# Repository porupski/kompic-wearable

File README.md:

# Kompic̄ &nbsp;·&nbsp; Mk1b

**Compact Open Multisensor Platform & Apparatus**

*/ˈkompitɕ/* — Croatian for "little computer" (and the word you'd only use for an actual friend, not a stranger).

A fully open-source, offline-first, ML-capable wrist-mounted sensor platform. The hardware collects. The firmware infers. You own everything.

> **Internal hardware version:** `iv8.0` — tracked in the docs to keep the PCBs matched across revisions.

Page: [https://porupski.github.io/kompic-wearable/](https://porupski.github.io/kompic-wearable/)

---

## What it is

Kompic̄ is a wrist-mounted sensor platform built around an **ESP32-S3** (dual-core, 8 MB PSRAM, 16 MB flash) with a sensor suite denser than any open-source watch, and enough on-device compute to run real neural networks on that data — sleep staging, sound classification, sensor fusion — all locally, all offline, all inspectable.

Currently on its second hardware revision, **Mk1b (`iv8.0`)**: all ten I²C sensors bring up clean, the AMOLED display and touch panel run a working LVGL interface, and GPS streams live fixes.

It is **not** a companion in the AI sense and **not** a phone accessory. It runs standalone. BLE is a capability, not a requirement. There is no cloud, no subscription, no account.

### Philosophy

- **Open source** — hardware (KiCad), firmware, ML models, and case design. Everything inspectable, modifiable, forkable.
- **Offline first** — works fully standalone. No phone, no cloud, no subscription.
- **Raw data access** — PPG waveforms, IMU streams, mic audio, environmental readings. Not just processed metrics.
- **ML-native** — the compute surplus exists specifically to run on-device inference.

---

## Hardware at a glance

| Domain | Detail |
|--------|--------|
| MCU | ESP32-S3 dual-core Xtensa LX7 @ 240 MHz, 8 MB PSRAM, 16 MB flash |
| Storage | MicroSD (128 GB+) |
| Connectivity | BLE 5.x |
| Display | 2.06" rectangular AMOLED, 45.6 × 37.3 mm glass, QSPI |
| PCBs | Two 1.0 mm 4-layer boards: main board + skin-facing daughter board |
| Case | Two-piece SLM titanium (Ti-6Al-4V), ~48 × 40 × 12 mm |
| Weight | 33 g watch body, 56 g with straps |
| Power | ~300 mAh LiPo, USB-C charging, fuel gauge |

### Sensor suite

| Sensor | Part | Measures |
|--------|------|----------|
| ❤️ Optical HR / SpO2 | MAX30101 | Heart rate, HRV, blood oxygen, PPG waveforms |
| 🏃 IMU | LSM6DSV16X | Accel, gyro, on-chip decision trees |
| 🔋 Fuel gauge | MAX17048G | Battery state-of-charge, cell voltage |
| 🌡️ Skin temperature | TMP117 | High-precision skin temp trending |
| 🧭 Magnetometer | LIS3MDLTR | Compass heading, magnetic anomaly |
| 🛰️ GPS | u-blox M10S | Position, velocity, atomic time sync |
| 🌍 Environmental | BME688 | Temp, pressure, humidity, VOC / air quality |
| 💡 Ambient light | VEML6030 | Lux level, display brightness |
| 🎤 MEMS microphone | MSM261DGT003 | Audio capture, noise level, sound classification |
| 📳 Haptics | ELV1411A + DRV2605L | Vibration patterns, alerts, smart wake |
| 🔦 Flashlight | White LED + BC847C driver | Utility light |
| 🚦 Status LED | RGB LED | Notification / mode indicator |

---

## Repository layout

```

kompic-wearable/
├── hardware/    KiCad schematics, PCB layout, production files   [CERN-OHL-S v2]
├── firmware/    ESP32-S3 dual-core firmware, ML models           [GPLv3]
├── case/        Onshape / 3D-printable case models               [CC BY-SA 4.0]
└── docs/        Documentation site (GitHub Pages) + images       [CC BY-SA 4.0]

```

---

## Project status

In active development. Hardware bring-up and verification underway for **Mk1b (`iv8.0`)**.

| Area | Status |
|------|--------|
| Circuit + PCB | Mk1 done (schematics, power tree, KiCad source) - needs update to Mk1b |
| Fabrication + assembly | Mk1 done (JLCPCB process, BOM, production files) - needs update to Mk1b |
| Manual assembly | Planned |
| 3D models + case | Planned ([View on Onshape](https://cad.onshape.com/documents/2e7ed980a6b60d585006763f/w/61a5aff226ec4b8dea793e41/e/49d622626b42dd5951f83a04?renderMode=0&uiState=6ab1d153fa1f2d90dd14641c)) |
| Firmware | In progress (I²C drivers, LVGL 9 display + touch UI, GPS UBX/NMEA parsing) |

Check the Development page for info on current stage of the project.

Documentation: **[https://porupski.github.io/kompic-wearable/](https://porupski.github.io/kompic-wearable/)**

---

## Author & License

Hardware, firmware, case, and webpage design by **Ivan Porupski**, 2026.

## License

Kompic̄ is released under three copyleft licenses, one per kind of material. All three keep the project open and require attribution — anyone may use, modify, build on, and even sell derivatives, **provided they keep their version equally open and credit the original author.**

| Part of the project | License | What it means in one line |
|---------------------|---------|---------------------------|
| **Hardware** (`/hardware`) | [CERN-OHL-S v2](https://ohwr.org/cern_ohl_s_v2.txt) | Make/modify/sell boards freely; distributed modifications must publish their full design files under the same license. |
| **Firmware** (`/firmware`) | [GPLv3](https://www.gnu.org/licenses/gpl-3.0.html) | Run/modify/redistribute freely; distributed modifications must publish full source under GPLv3. |
| **Docs & 3D / case** (`/docs`, `/case`) | [CC BY-SA 4.0](https://creativecommons.org/licenses/by-sa/4.0/) | Reuse/remix freely with credit; shared derivatives stay under CC BY-SA. |

GitHub displays **GPL-3.0** as the repository's headline license; the per-folder breakdown above is authoritative. See [`LICENSING.md`](LICENSING.md) for details.

**Copyright © 2026 Ivan Porupski.** Each contributor retains copyright on their own contributions; the whole project remains under the copyleft licenses above.

There is no separate commercial license and no contributor license agreement (CLA). Contributions are accepted under the same licenses as the files they touch (inbound = outbound).

---

## Contributing

Contributions are welcome. By submitting a contribution you agree it is licensed under the same license that already covers the file(s) you are changing (see table above). Keep copyright and license notices intact.

---

## Disclaimer

Kompic̄ is **not a medical device** and is not intended to diagnose, treat, or prevent any condition. All work with these electronics and lithium batteries is done at your own risk. The author and contributors are not liable for any direct, indirect, incidental, or consequential damages.

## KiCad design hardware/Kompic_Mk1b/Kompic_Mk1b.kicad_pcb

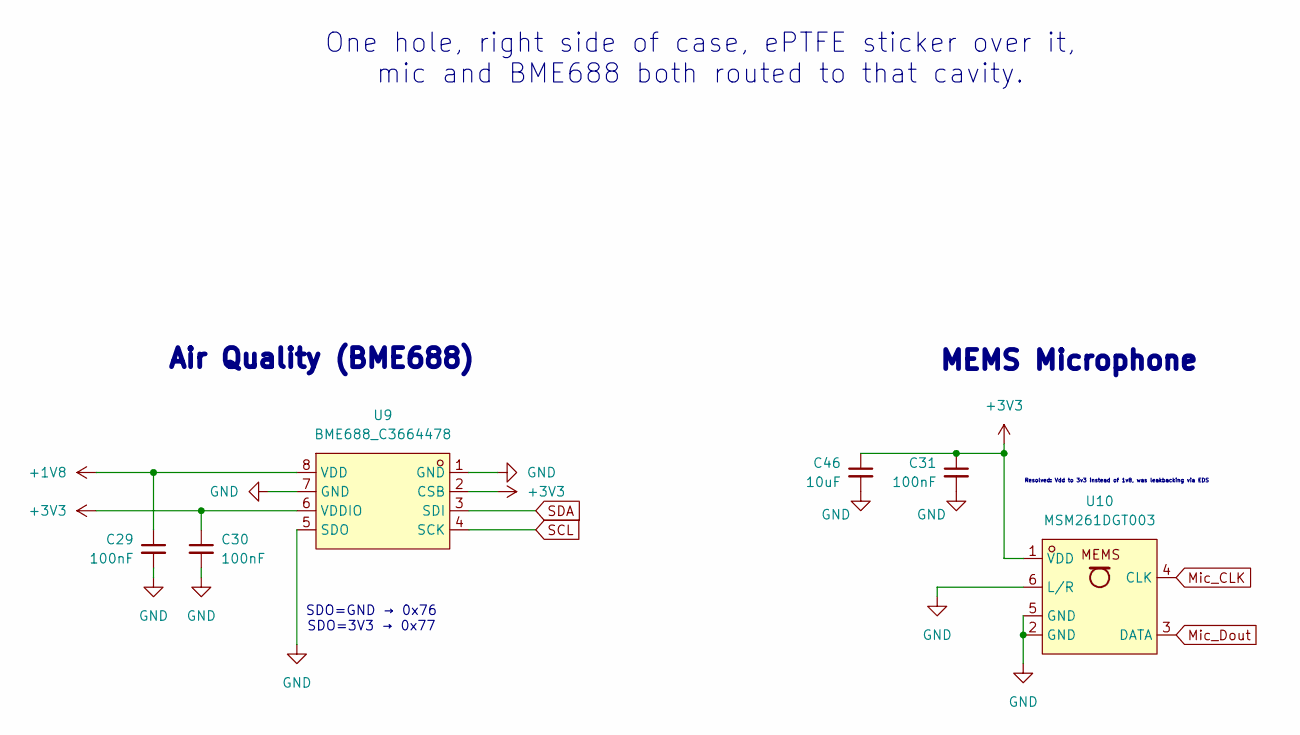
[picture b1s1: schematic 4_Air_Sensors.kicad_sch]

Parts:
C29, C30, C31: 100nF; C_0402_1005Metric_Pad0.74x0.62mm_HandSolder
C46: 10uF; C_0402_1005Metric_Pad0.74x0.62mm_HandSolder
U9: BME688_C3664478; LGA-8_L3.0-W3.0-P0.80_BME688; LCSC Part C3664478
U10: MSM261DGT003; MIC-SMD_6P-L4.0-W2.0_LMD4020T261-OC3; LCSC Part C48227730

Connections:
+1V8: C29.1, U9.8 (VDD); also elsewhere on the board
+3V3: C30.1, C31.1, C46.1, U9.2 (CSB), U9.6 (VDDIO), U10.1 (VDD); also elsewhere on the board
GND: C29.2, C30.2, C31.2, C46.2, U9.1 (GND), U9.5 (SDO), U9.7 (GND), U10.2 (GND), U10.5 (GND), U10.6 (L/R); also elsewhere on the board
Mic_CLK: U10.4 (CLK); also elsewhere on the board
Mic_Dout: U10.3 (DATA); also elsewhere on the board
SCL: U9.4 (SCK); also elsewhere on the board
SDA: U9.3 (SDI); also elsewhere on the board

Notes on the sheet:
Air Quality (BME688)
SDO=GND → 0x76 SDO=3V3 → 0x77
One hole, right side of case, ePTFE sticker over it, mic and BME688 both routed to that cavity.
MEMS Microphone
Resolved: Vdd to 3v3 instead of 1v8, was leakbacking via EDS

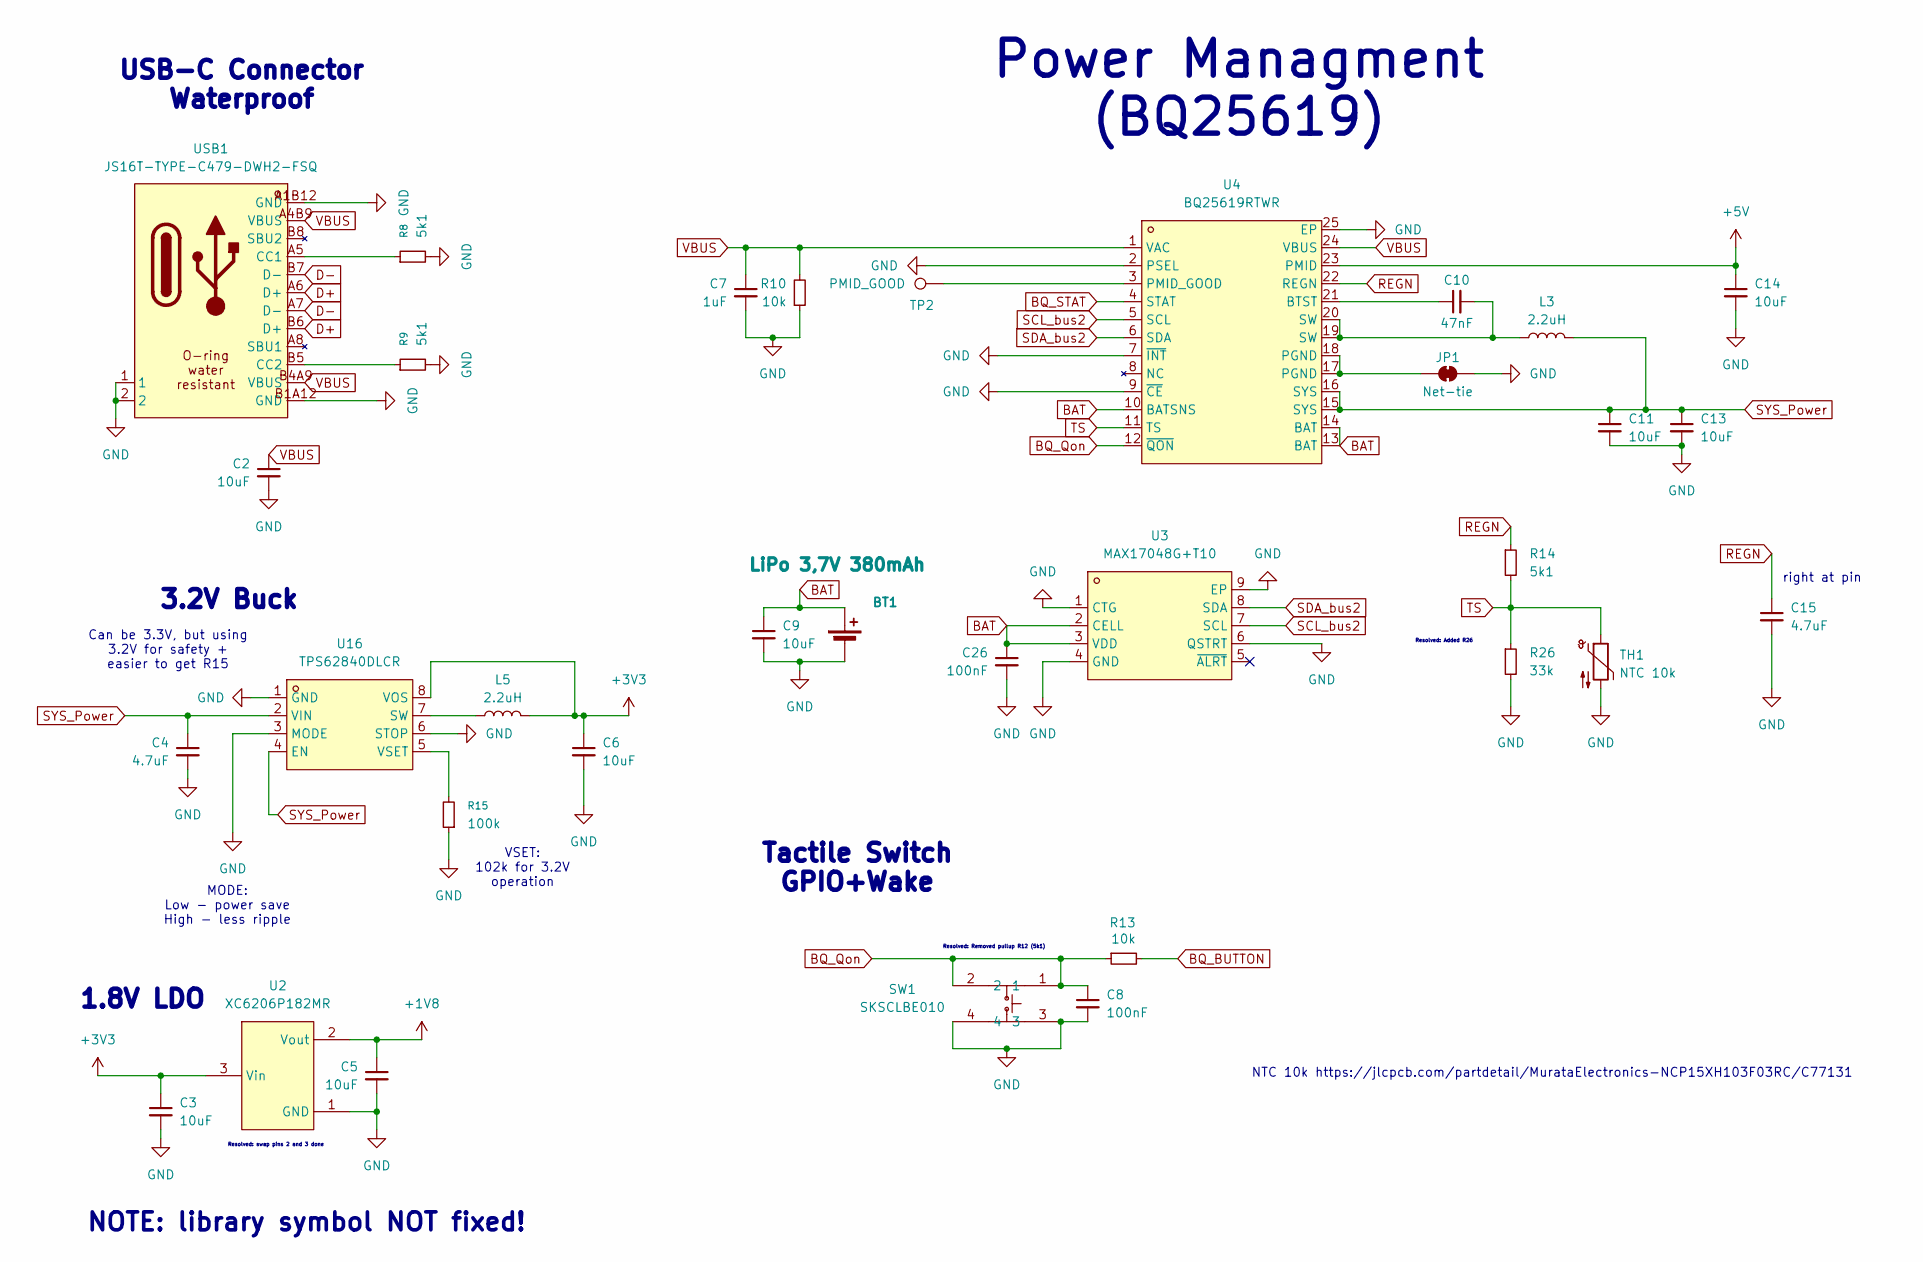
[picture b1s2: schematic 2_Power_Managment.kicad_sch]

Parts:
BT1: LiPo 3,7V 380mAh; Battery_solder_terminals_v1
C2, C3, C5, C6, C9, C11, C13, C14: 10uF; C_0402_1005Metric_Pad0.74x0.62mm_HandSolder
C4, C15: 4.7uF; C_0402_1005Metric_Pad0.74x0.62mm_HandSolder
C7: 1uF; C_0402_1005Metric_Pad0.74x0.62mm_HandSolder
C8, C26: 100nF; C_0402_1005Metric_Pad0.74x0.62mm_HandSolder
C10: 47nF; C_0603_1608Metric_Pad1.08x0.95mm_HandSolder
JP1: Net-tie; SolderJumper-2_P1.3mm_Bridged_RoundedPad1.0x1.5mm
L3, L5: 2.2uH; L_1008_2520Metric
R8, R9, R14: 5k1; R_0402_1005Metric_Pad0.72x0.64mm_HandSolder
R10, R13: 10k; R_0402_1005Metric_Pad0.72x0.64mm_HandSolder
R15: 100k; R_0402_1005Metric_Pad0.72x0.64mm_HandSolder
R26: 33k; R_0402_1005Metric_Pad0.72x0.64mm_HandSolder
SW1: SKSCLBE010; KEY-SMD_4P-SKSCLXX010; LCSC Part C115361
TH1: NTC 10k; R_0402_1005Metric_Pad0.72x0.64mm_HandSolder
TP2: PMID_GOOD; TestPoint_Pad_D1.0mm
U2: XC6206P182MR; SOT-23-3_L2.9-W1.6-P1.90-LS2.8-BR; LCSC Part C21659
U3: MAX17048G+T10; TDFN-8_L2.0-W2.0-P0.50-BL-EP1.2; MPN MAX17048G+T10; LCSC Part C2682616
U4: BQ25619RTWR; WQFN-24_L4.0-W4.0-P0.50-TL-EP2.7; LCSC Part C2864534
U16: TPS62840DLCR; VSON-8_L2.0-W1.5-P0.50-BL; LCSC Part C2071859
USB1: JS16T-TYPE-C479-DWH2-FSQ; USB-C-SMD_JS16T-TYPE-C479-DWH2-FSQ; LCSC Part C49118447

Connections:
+1V8: C5.1, U2.2 (Vout); also elsewhere on the board
+3V3: C3.1, C6.1, L5.2, U2.3 (Vin), U16.8 (VOS); also elsewhere on the board
+5V: C14.1, U4.23 (PMID); also elsewhere on the board
BAT: BT1.1 (+), C9.1, C26.1, U3.2 (CELL), U3.3 (VDD), U4.10 (BATSNS), U4.13 (BAT), U4.14 (BAT)
BQ_BUTTON: R13.2; also elsewhere on the board
BQ_Qon: C8.1, R13.1, SW1.1, SW1.2, U4.12 (~QON)
BQ_STAT: U4.4 (STAT); also elsewhere on the board
D+: USB1.A6 (D+), USB1.B6 (D+); also elsewhere on the board
D-: USB1.A7 (D-), USB1.B7 (D-); also elsewhere on the board
GND: BT1.2 (-), C2.2, C3.2, C4.2, C5.2, C6.2, C7.2, C8.2, C9.2, C11.2, C13.2, C14.2, C15.2, C26.2, JP1.2 (B), R8.2, R9.2, R10.1, R15.1, R26.2, SW1.3, SW1.4, TH1.2, U2.1 (GND), U3.1 (CTG), U3.4 (GND), U3.6 (QSTRT), U3.9 (EP), U4.2 (PSEL), U4.7 (~INT), U4.9 (~CE), U4.25 (EP), U16.1 (GND), U16.3 (MODE), U16.6 (STOP), USB1.1, USB1.2, USB1.A1B12 (GND), USB1.B1A12 (GND); also elsewhere on the board
unnamed: C10.2, L3.1, U4.19 (SW), U4.20 (SW)
unnamed: JP1.1 (A), U4.17 (PGND), U4.18 (PGND)
unnamed: C10.1, U4.21 (BTST)
unnamed: TP2.1 (1_1), U4.3 (PMID_GOOD)
unnamed: L5.1, U16.7 (SW)
unnamed: R15.2, U16.5 (VSET)
unnamed: R8.1, USB1.A5 (CC1)
unnamed: R9.1, USB1.B5 (CC2)
REGN: C15.1, R14.1, U4.22 (REGN)
SCL_bus2: U3.7 (SCL), U4.5 (SCL); also elsewhere on the board
SDA_bus2: U3.8 (SDA), U4.6 (SDA); also elsewhere on the board
SYS_Power: C4.1, C11.1, C13.1, L3.2, U4.15 (SYS), U4.16 (SYS), U16.2 (VIN), U16.4 (EN)
TS: R14.2, R26.1, TH1.1, U4.11 (TS)
VBUS: C2.1, C7.1, R10.2, U4.1 (VAC), U4.24 (VBUS), USB1.A4B9 (VBUS), USB1.B4A9 (VBUS)

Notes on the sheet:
right at pin
Tactile Switch GPIO+Wake
3.2V Buck
Resolved: swap pins 2 and 3 done
Power Managment (BQ25619)
NTC 10k https://jlcpcb.com/partdetail/MurataElectronics-NCP15XH103F03RC/C77131
NOTE: library symbol NOT fixed!
USB-C Connector Waterproof
Resolved: Removed pullup R12 (5k1)
VSET: 102k for 3.2V operation
MODE: Low - power save High - less ripple
Can be 3.3V, but using 3.2V for safety + easier to get R15
Resolved: Added R26
1.8V LDO

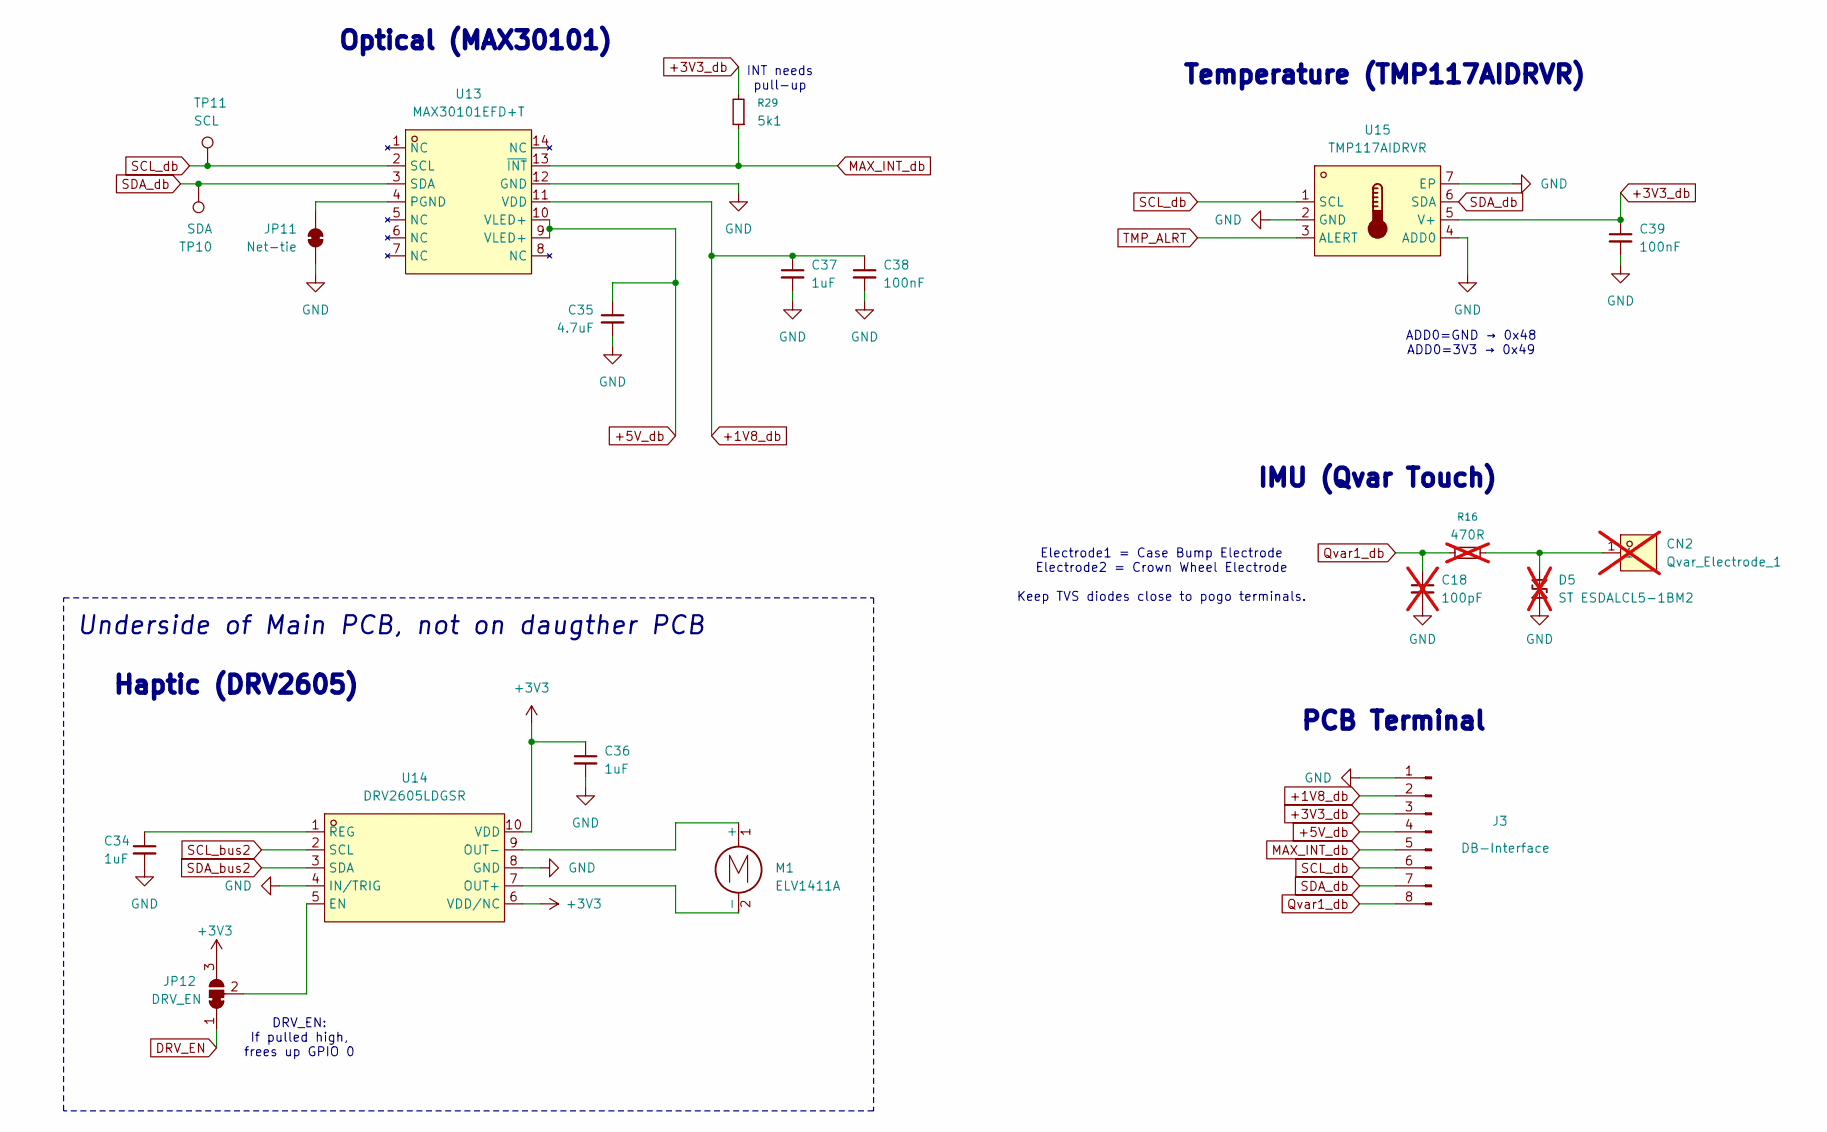
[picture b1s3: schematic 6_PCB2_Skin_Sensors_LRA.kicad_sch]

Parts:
C18: 100pF; C_0402_1005Metric_Pad0.74x0.62mm_HandSolder; not fitted
C34, C36, C37: 1uF; C_0402_1005Metric_Pad0.74x0.62mm_HandSolder
C35: 4.7uF; C_0402_1005Metric_Pad0.74x0.62mm_HandSolder
C38, C39: 100nF; C_0402_1005Metric_Pad0.74x0.62mm_HandSolder
CN2: Qvar_Electrode_1; TestPoint_Pad_D3.0mm; MPN YZR0028-15020-01; LCSC Part C7429439; not fitted
D5: ST ESDALCL5-1BM2; D_SOD-882; not fitted
J3: DB-Interface; Custom_8_pin_for_SmartWatch_v4-DB-semicircle
JP11: Net-tie; SolderJumper-2_P1.3mm_Bridged_RoundedPad1.0x1.5mm
JP12: DRV_EN; SolderJumper-3_P1.3mm_Bridged2Bar12_RoundedPad1.0x1.5mm
M1: ELV1411A; Battery_solder_terminals_v1
R16: 470R; R_0402_1005Metric_Pad0.72x0.64mm_HandSolder; not fitted
R29: 5k1; R_0402_1005Metric_Pad0.72x0.64mm_HandSolder
TP10: SDA; TestPoint_Pad_1.0x1.0mm
TP11: SCL; TestPoint_Pad_1.0x1.0mm
U13: MAX30101EFD+T; OESIP-14_L5.6-W3.3-P0.80-TL; LCSC Part C2859066
U14: DRV2605LDGSR; VSSOP-10_L3.0-W3.0-P0.50-LS4.9-BL; LCSC Part C527464
U15: TMP117AIDRVR; WSON-6_L2.0-W2.0-P0.65-TL-EP; LCSC Part C699536

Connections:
+1V8_db: C37.1, C38.1, J3.2, U13.11 (VDD)
+3V3: C36.1, JP12.3 (B), U14.6 (VDD/NC), U14.10 (VDD); also elsewhere on the board
+3V3_db: C39.1, J3.3, R29.2, U15.5 (V+)
+5V_db: C35.1, J3.4, U13.9 (VLED+), U13.10 (VLED+)
DRV_EN: JP12.1 (A); also elsewhere on the board
GND: C18.2, C34.2, C35.2, C36.2, C37.2, C38.2, C39.2, D5.1 (A1), J3.1, JP11.1 (A), U13.12 (GND), U14.4 (IN/TRIG), U14.8 (GND), U15.2 (GND), U15.4 (ADD0), U15.7 (EP); also elsewhere on the board
MAX_INT_db: J3.5, R29.1, U13.13 (~INT)
unnamed: CN2.1 (1_1), D5.2 (A2), R16.2
unnamed: JP11.2 (B), U13.4 (PGND)
unnamed: JP12.2 (C), U14.5 (EN)
unnamed: M1.1 (+), U14.9 (OUT-)
unnamed: M1.2 (-), U14.7 (OUT+)
unnamed: C34.1, U14.1 (REG)
Qvar1_db: C18.1, J3.8, R16.1
SCL_bus2: U14.2 (SCL); also elsewhere on the board
SCL_db: J3.6, TP11.1 (1_1), U13.2 (SCL), U15.1 (SCL)
SDA_bus2: U14.3 (SDA); also elsewhere on the board
SDA_db: J3.7, TP10.1 (1_1), U13.3 (SDA), U15.6 (SDA)
TMP_ALRT: U15.3 (ALERT); also elsewhere on the board

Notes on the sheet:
Underside of Main PCB, not on daugther PCB
IMU (Qvar Touch)
INT needs pull-up
PCB Terminal
Haptic (DRV2605)
Electrode1 = Case Bump Electrode Electrode2 = Crown Wheel Electrode Keep TVS diodes close to pogo terminals.
Optical (MAX30101)
DRV_EN: If pulled high, frees up GPIO 0
ADD0=GND → 0x48 ADD0=3V3 → 0x49
Temperature (TMP117AIDRVR)

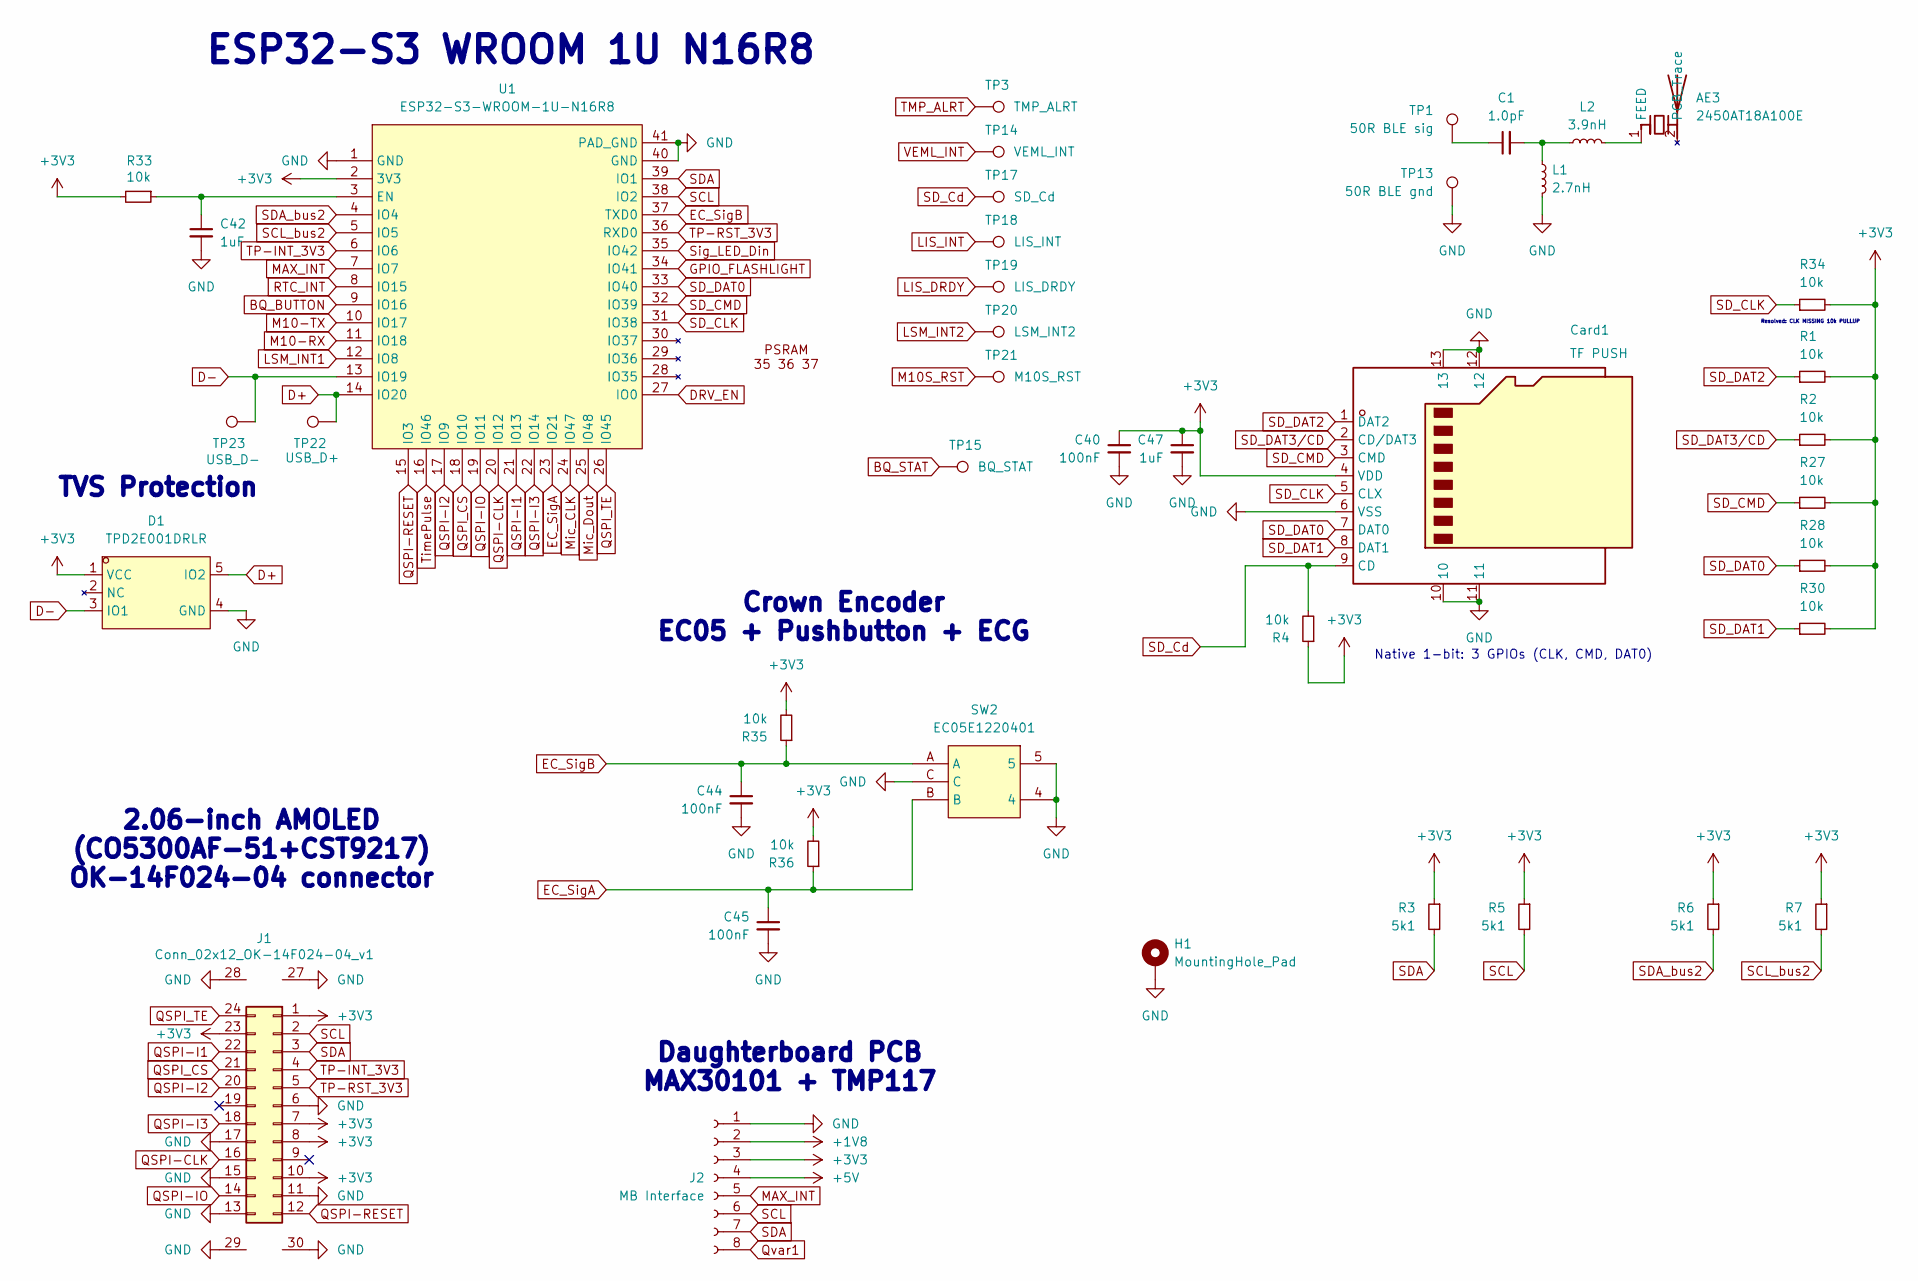
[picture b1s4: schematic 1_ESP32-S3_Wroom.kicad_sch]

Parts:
AE3: 2450AT18A100E; ANT-SMD_L3.2-W1.6; LCSC Part C89334
C1: 1.0pF; C_0402_1005Metric_Pad0.74x0.62mm_HandSolder
C40, C44, C45: 100nF; C_0402_1005Metric_Pad0.74x0.62mm_HandSolder
C42, C47: 1uF; C_0402_1005Metric_Pad0.74x0.62mm_HandSolder
Card1: TF PUSH; TF-SMD_TF-PUSH; LCSC Part C393941
D1: TPD2E001DRLR; SOT-553-5_L1.6-W1.2-P0.50-LS1.6-BR; LCSC Part C150526
H1: MountingHole_Pad; MountingHole_2.2mm_M2_DIN965_Pad_TopOnly
J1: Conn_02x12_OK-14F024-04_v1; Connector_b2b_OK-F024-04_v1
J2: MB Interface; Custom_8_pin_for_SmartWatch_v4-MB-straightline
L1: 2.7nH; L_0402_1005Metric
L2: 3.9nH; L_0402_1005Metric
R1, R2, R4, R27, R28, R30, R33, R34, R35, R36: 10k; R_0402_1005Metric_Pad0.72x0.64mm_HandSolder
R3, R5, R6, R7: 5k1; R_0402_1005Metric_Pad0.72x0.64mm_HandSolder
SW2: EC05E1220401; SW-SMD_EC05E1220401-CUSTOM-ORIENT_v1; MPN EC05E1220401; LCSC Part C116648
TP1: 50R BLE sig; TestPoint_Pad_D1.0mm
TP3: TMP_ALRT; TestPoint_Pad_D1.0mm
TP13: 50R BLE gnd; TestPoint_Pad_D1.0mm
TP14: VEML_INT; TestPoint_Pad_D1.0mm
TP15: BQ_STAT; TestPoint_Pad_D1.0mm
TP17: SD_Cd; TestPoint_Pad_D1.0mm
TP18: LIS_INT; TestPoint_Pad_D1.0mm
TP19: LIS_DRDY; TestPoint_Pad_D1.0mm
TP20: LSM_INT2; TestPoint_Pad_D1.0mm
TP21: M10S_RST; TestPoint_Pad_D1.0mm
TP22: USB_D+; TestPoint_Pad_D1.0mm
TP23: USB_D-; TestPoint_Pad_D1.0mm
U1: ESP32-S3-WROOM-1U-N16R8; WIRELM-SMD_ESP32-S3-WROOM-1U; LCSC Part C3013946

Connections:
+1V8: J2.2; also elsewhere on the board
+3V3: C40.1, C47.1, Card1.4 (VDD), D1.1 (VCC), J1.1, J1.7, J1.8, J1.10, J1.23, J2.3, R1.2, R2.2, R3.1, R4.1, R5.1, R6.1, R7.1, R27.2, R28.2, R30.2, R33.2, R34.2, R35.2, R36.2, U1.2 (3V3); also elsewhere on the board
+5V: J2.4; also elsewhere on the board
BQ_BUTTON: U1.9 (IO16); also elsewhere on the board
BQ_STAT: TP15.1 (1_1); also elsewhere on the board
D+: D1.5 (IO2), TP22.1 (1_1), U1.14 (IO20); also elsewhere on the board
D-: D1.3 (IO1), TP23.1 (1_1), U1.13 (IO19); also elsewhere on the board
DRV_EN: U1.27 (IO0); also elsewhere on the board
EC_SigA: C45.1, R36.1, SW2.B, U1.23 (IO21)
EC_SigB: C44.1, R35.1, SW2.A, U1.37 (TXD0)
GND: C40.2, C42.2, C44.2, C45.2, C47.2, Card1.6 (VSS), Card1.10, Card1.11, Card1.12, Card1.13, D1.4 (GND), H1.1 (1_1), J1.6, J1.11, J1.13, J1.15, J1.17, J1.27, J1.28, J1.29, J1.30, J2.1, L1.2, SW2.4, SW2.5, SW2.C, TP13.1 (1_1), U1.1 (GND), U1.40 (GND), U1.41 (PAD_GND); also elsewhere on the board
GPIO_FLASHLIGHT: U1.34 (IO41); also elsewhere on the board
LIS_DRDY: TP19.1 (1_1); also elsewhere on the board
LIS_INT: TP18.1 (1_1); also elsewhere on the board
LSM_INT1: U1.12 (IO8); also elsewhere on the board
LSM_INT2: TP20.1 (1_1); also elsewhere on the board
M10-RX: U1.11 (IO18); also elsewhere on the board
M10-TX: U1.10 (IO17); also elsewhere on the board
M10S_RST: TP21.1 (1_1); also elsewhere on the board
MAX_INT: J2.5, U1.7 (IO7)
Mic_CLK: U1.24 (IO47); also elsewhere on the board
Mic_Dout: U1.25 (IO48); also elsewhere on the board
unnamed: AE3.1 (FEED_1), L2.2
unnamed: C1.1, TP1.1 (1_1)
unnamed: C1.2, L1.1, L2.1
unnamed: C42.1, R33.1, U1.3 (EN)
QSPI-CLK: J1.16, U1.20 (IO12)
QSPI-I1: J1.22, U1.21 (IO13)
QSPI-I2: J1.20, U1.17 (IO9)
QSPI-I3: J1.18, U1.22 (IO14)
QSPI-IO: J1.14, U1.19 (IO11)
QSPI-RESET: J1.12, U1.15 (IO3)
QSPI_CS: J1.21, U1.18 (IO10)
QSPI_TE: J1.24, U1.26 (IO45)
Qvar1: J2.8; also elsewhere on the board
RTC_INT: U1.8 (IO15); also elsewhere on the board
SCL: J1.2, J2.6, R5.2, U1.38 (IO2); also elsewhere on the board
SCL_bus2: R7.2, U1.5 (IO5); also elsewhere on the board
SDA: J1.3, J2.7, R3.2, U1.39 (IO1); also elsewhere on the board
SDA_bus2: R6.2, U1.4 (IO4); also elsewhere on the board
SD_CLK: Card1.5 (CLX), R34.1, U1.31 (IO38)
SD_CMD: Card1.3 (CMD), R27.1, U1.32 (IO39)
SD_Cd: Card1.9 (CD), R4.2, TP17.1 (1_1)
SD_DAT0: Card1.7 (DAT0), R28.1, U1.33 (IO40)
SD_DAT1: Card1.8 (DAT1), R30.1
SD_DAT2: Card1.1 (DAT2), R1.1
SD_DAT3/CD: Card1.2 (CD/DAT3), R2.1
Sig_LED_Din: U1.35 (IO42); also elsewhere on the board
TMP_ALRT: TP3.1 (1_1); also elsewhere on the board
TP-INT_3V3: J1.4, U1.6 (IO6)
TP-RST_3V3: J1.5, U1.36 (RXD0)
TimePulse: U1.16 (IO46); also elsewhere on the board
VEML_INT: TP14.1 (1_1); also elsewhere on the board

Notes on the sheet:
Crown Encoder EC05 + Pushbutton + ECG
TVS Protection
Resolved: CLK MISSING 10k PULLUP
ESP32-S3 WROOM 1U N16R8
2.06-inch AMOLED (CO5300AF-51+CST9217) OK-14F024-04 connector
Daughterboard PCB MAX30101 + TMP117
Native 1-bit: 3 GPIOs (CLK, CMD, DAT0)

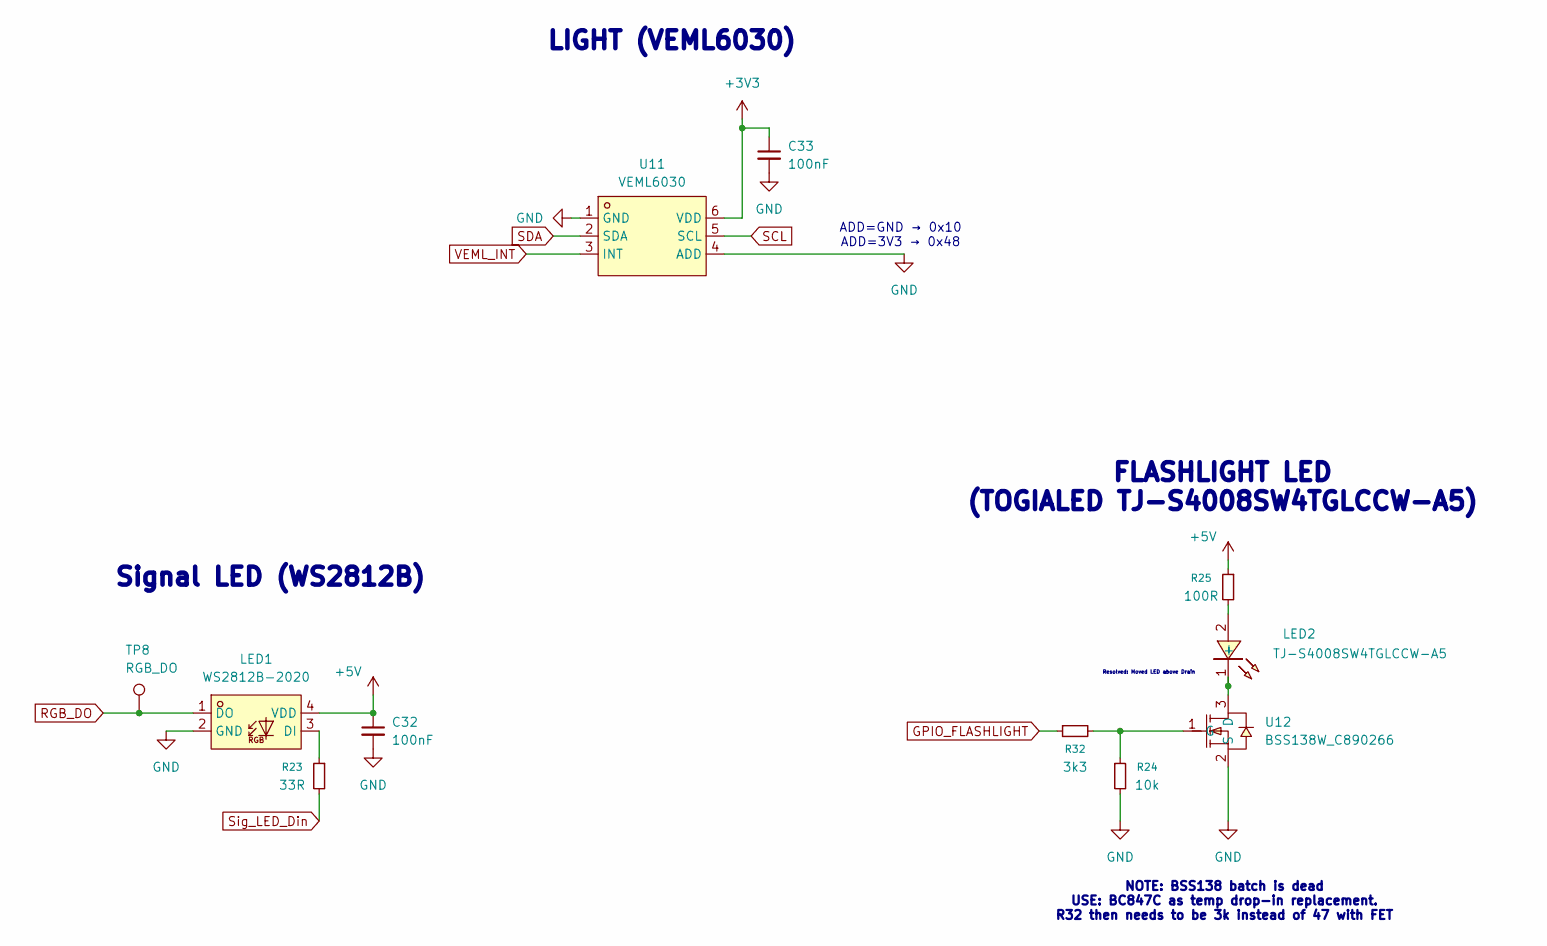
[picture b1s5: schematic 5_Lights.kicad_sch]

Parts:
C32, C33: 100nF; C_0402_1005Metric_Pad0.74x0.62mm_HandSolder
LED1: WS2812B-2020; LED-SMD_4P-L2.0-W2.0-TL_WS2812B-2020; LCSC Part C965555
LED2: TJ-S4008SW4TGLCCW-A5; LED-SMD_TJ-S4008SW4TGLCCW-A5; LCSC Part C601698
R23: 33R; R_0402_1005Metric_Pad0.72x0.64mm_HandSolder
R24: 10k; R_0402_1005Metric_Pad0.72x0.64mm_HandSolder
R25: 100R; R_0402_1005Metric_Pad0.72x0.64mm_HandSolder
R32: 3k3; R_0402_1005Metric_Pad0.72x0.64mm_HandSolder
TP8: RGB_DO; TestPoint_Pad_1.0x1.0mm
U11: VEML6030; SENSORS-SMD_VEML6030; LCSC Part C132182
U12: BSS138W_C890266; SC-70-3_L2.0-W1.3-P0.65-LS2.1-BL; LCSC Part C890266

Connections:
+3V3: C33.1, U11.6 (VDD); also elsewhere on the board
+5V: C32.1, LED1.4 (VDD), R25.1; also elsewhere on the board
GND: C32.2, C33.2, LED1.2 (GND), R24.2, U11.1 (GND), U11.4 (ADD), U12.2 (S); also elsewhere on the board
GPIO_FLASHLIGHT: R32.1; also elsewhere on the board
unnamed: LED1.3 (DI), R23.1
unnamed: LED2.2 (+), R25.2
unnamed: LED2.1 (-), U12.3 (D)
unnamed: R24.1, R32.2, U12.1 (G)
RGB_DO: LED1.1 (DO), TP8.1 (1_1)
SCL: U11.5 (SCL); also elsewhere on the board
SDA: U11.2 (SDA); also elsewhere on the board
Sig_LED_Din: R23.2; also elsewhere on the board
VEML_INT: U11.3 (INT); also elsewhere on the board

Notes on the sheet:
Signal LED (WS2812B)
LIGHT (VEML6030)
ADD=GND → 0x10 ADD=3V3 → 0x48
FLASHLIGHT LED (TOGIALED TJ-S4008SW4TGLCCW-A5)
Resolved: Moved LED above Drain
NOTE: BSS138 batch is dead USE: BC847C as temp drop-in replacement. R32 then needs to be 3k instead of 47 with FET
